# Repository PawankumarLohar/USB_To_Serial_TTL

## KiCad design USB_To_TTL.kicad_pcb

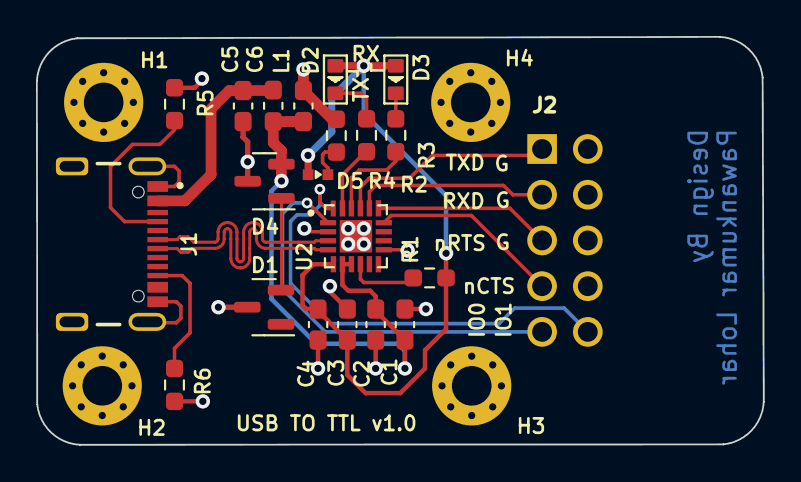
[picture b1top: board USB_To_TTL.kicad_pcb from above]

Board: 2 copper layers, 40.4 x 22.7 mm, 25 parts (0 on the bottom side), 20 nets.

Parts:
C1, C2, C3, C4, C5, C6: C; C_0603_1608Metric_Pad1.08x0.95mm_HandSolder
D1, D4: SM712_SOT23; SOT-23
D2, D3: LED-SMD-RED-DIFFUSED_0603_; LED-0603
D5: 5988A80107F; LED_5988A80107F
H1, H2, H3, H4: MountingHole_Pad; MountingHole_2.2mm_M2_Pad_Via
J1: USB4105GFA120; GCT_USB4105GFA120
J2: 61201021721; SHDRRA10W64P254X254_2X5_2036X885X910P
L1: L_Ferrite; L_0603_1608Metric_Pad1.05x0.95mm_HandSolder
R1, R2, R3, R4: 1K; R_0603_1608Metric_Pad0.98x0.95mm_HandSolder
R5, R6: 5.1K; R_0603_1608Metric_Pad0.98x0.95mm_HandSolder
U2: CP2102N-Axx-xQFN20; SILABS_CP2102N-A02-GQFN20R

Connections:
3.3V: C3.1, C4.1, D2.+, D3.+, D5.2 (A), R1.1, U2.6 (VDD)
CC1: J1.A5 (CC1), R5.1
CC2: J1.B5 (CC2), R6.1
D+: D4.1 (A1), J1.A6 (DP1), U2.4 (D+)
D-: D1.2 (A2), J1.A7 (DN1), U2.5 (D-)
GND: C1.2, C2.2, C3.2, C4.2, C5.2, C6.2, D1.3 (common), D4.3 (common), J1.A1_B12 (GND), J1.B1_A12 (GND), J1.SH1 (SHELL_GND), J1.SH2 (SHELL_GND), J1.SH3 (SHELL_GND), J1.SH4 (SHELL_GND), J2.2, J2.4, J2.6, J2.8, R4.2, R5.2, R6.2, U2.3 (GND), U2.12 (GND), U2.21 (GND)
GPIO0.1: J2.10, U2.1 (RS485/GPIO.1)
GPIO.0: J2.9, U2.2 (CLK/GPIO.0)
unnamed: C5.1, J1.A4_B9 (VBUS), L1.1
unnamed: D2.-, R2.1
unnamed: D3.-, R3.1
unnamed: D5.1 (K), R4.1
unnamed: R1.2, U2.9 (~RST)
RXD: J2.3, U2.17 (RXD)
TXD: J2.1, U2.18 (TXD)
VBUS: C1.1, C2.1, C6.1, D4.2 (A2), L1.2, U2.7 (VREGIN), U2.8 (VBUS)
nCTS: J2.7, U2.15 (~CTS)
nRTS: J2.5, U2.16 (~RTS)
nRXT: R3.2, U2.19 (~RXT/GPIO.3)
nTXT: R2.2, U2.20 (~TXT/GPIO.2)

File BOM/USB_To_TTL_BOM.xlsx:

Item | Qty | Reference(s) | Value | Per unit price(in Rupees) | Price as per quantity | Footprint
1 | 2 | C1, C3 | 4.7uF | 2.4 | 4.8 | Capacitor_SMD:C_0603_1608Metric_Pad1.08x0.95mm_HandSolder
2 | 4 | C2, C4, C5, C6 | 100nF | 1.37 | 5.48 | Capacitor_SMD:C_0603_1608Metric_Pad1.08x0.95mm_HandSolder
3 | 2 | D1, D4 | SM712_SOT23 | 17.59 | 35.18 | Package_TO_SOT_SMD:SOT-23
4 | 2 | D2, D3 | LED-SMD-RED-DIFFUSED_0603_ | 2.5099999999999998 | 5.0199999999999996 | LED-SMD-RED-DIFFUSED_0603_:LED-0603
5 | 1 | D5 | 5988A80107F | 22.6 | 22.6 | LED_5988A80107F:LED_5988A80107F
6 | 4 | H1, H2, H3, H4 | MountingHole_Pad | 0 | 0 | MountingHole:MountingHole_2.2mm_M2_Pad_Via
7 | 1 | J1 | USB4105GFA120 | 18.899999999999999 | 18.899999999999999 | USB4105GFA120:GCT_USB4105GFA120
8 | 1 | J2 | 61201021721 | 9.56 | 9.56 | LIB_61201021721:SHDRRA10W64P254X254_2X5_2036X885X910P
9 | 1 | L1 | 120R | 1.19 | 1.19 | Inductor_SMD:L_0603_1608Metric_Pad1.05x0.95mm_HandSolder
10 | 4 | R1, R2, R3, R4 | 1K | 0.39 | 1.56 | Resistor_SMD:R_0603_1608Metric_Pad0.98x0.95mm_HandSolder
11 | 2 | R5, R6 | 5.1K | 0.39 | 0.78 | Resistor_SMD:R_0603_1608Metric_Pad0.98x0.95mm_HandSolder
12 | 1 | U2 | CP2102N-Axx-xQFN20 | 200 | 200 | CP2102N-A02-GQFN20R:SILABS_CP2102N-A02-GQFN20R
 |  |  |  | Total | 305.07

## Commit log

2024-03-23 Create README.md
    PCB Images added in README
2024-03-23 Added Kicad project files
